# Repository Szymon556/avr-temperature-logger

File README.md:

# AVR Temperature Logger

Temperature logging system based on ATmega328P with:
- DS18B20 temperature sensor
- AT45DB041 DataFlash memory
- HD44780 LCD display

## Features

- Temperature acquisition
- SPI DataFlash storage
- LCD visualization
- AVR-GCC + Makefile build system avr-temperature-logger

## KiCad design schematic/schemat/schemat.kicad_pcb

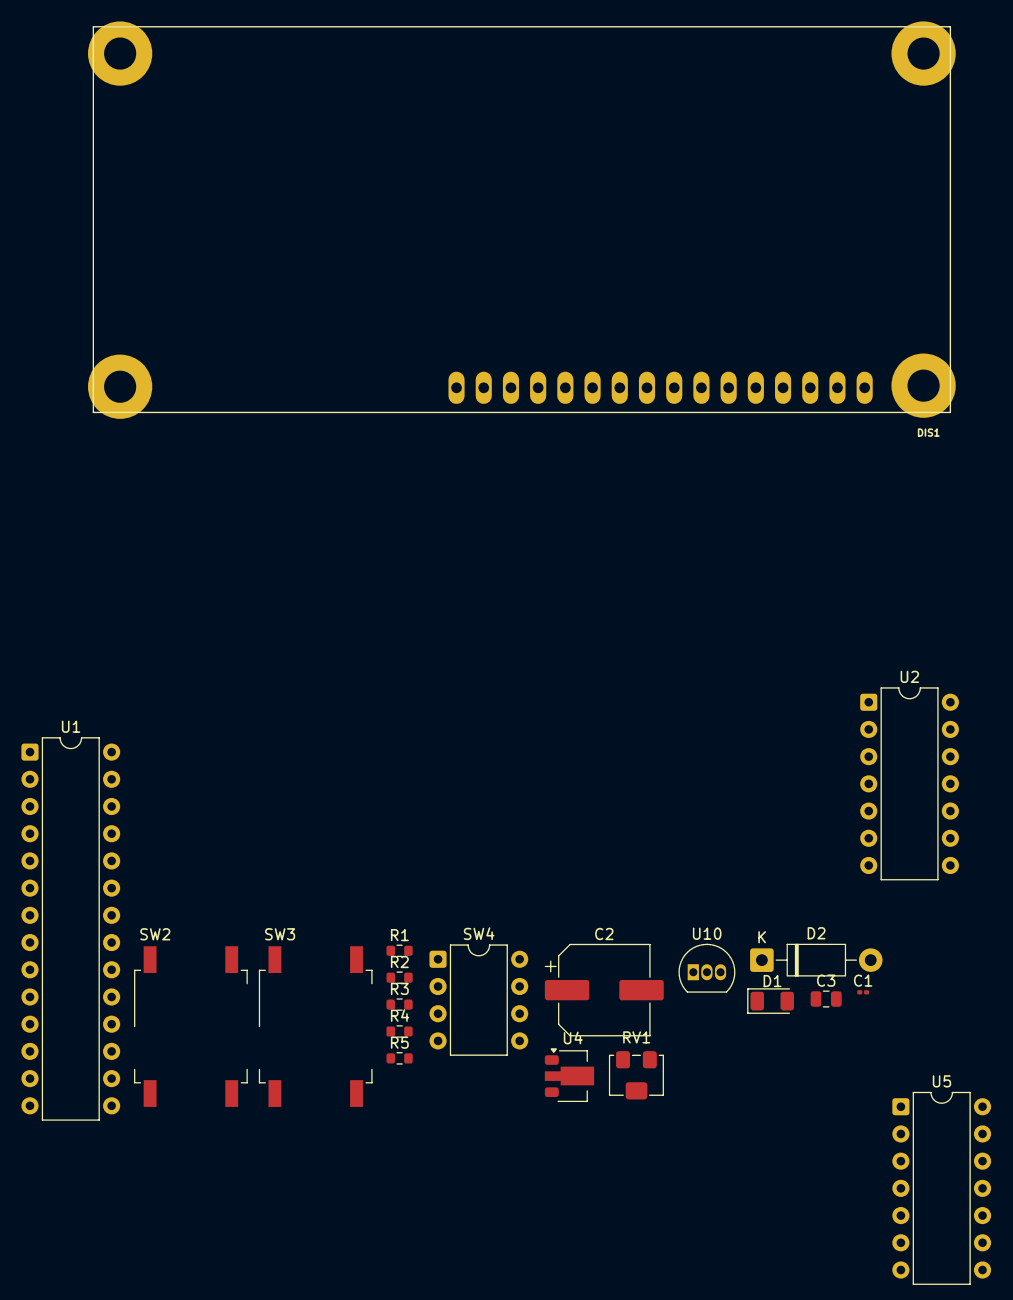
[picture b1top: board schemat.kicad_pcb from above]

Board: 2 copper layers, 20 parts (0 on the bottom side), 24 nets, no tracks yet.

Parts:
C1: 0.1uF; C_0201_0603Metric
C2: 1uF; CP_Elec_8x6.9
C3: 10uF; C_0805_2012Metric
D1: IR26-21C_L110_TR8; LED_1206_3216Metric
D2: 1N4001; D_DO-41_SOD81_P10.16mm_Horizontal
DIS1: HD44780; 16026-16X2
R1, R4: 100k; R_0603_1608Metric
R2: R_Trim; R_0603_1608Metric
R3, R5: 1k; R_0603_1608Metric
RV1: R_Potentiometer; Potentiometer_Bourns_3224W_Vertical
SW2, SW3: SW_MEC_5G; SW_MEC_5GSH9
SW4: SW_DIP_x01; DIP-8_W7.62mm
U1: ATmega328-P; DIP-28_W7.62mm
U2, U5: 74LS06; DIP-14_W7.62mm
U4: LM317L_SOT-89; SOT-89-3
U10: DS18B20; TO-92_Inline

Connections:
3.3V: C2.1, D1.2 (A), D2.2 (A), R1.1, R4.1, U4.2 (VO)
+5V: C3.1, DIS1.P$2, DIS1.P$15, R5.1, RV1.3, SW4.1, U1.7 (VCC), U1.20 (AVCC), U1.21 (AREF), U10.3 (V_{DD})
CS_High: U1.11 (PD5), U2.5
D4: DIS1.P$11, U1.27 (PC4)
D5: DIS1.P$12, U1.26 (PC3)
D6: DIS1.P$13, U1.25 (PC2)
D7: DIS1.P$14, U1.28 (PC5)
E: DIS1.P$6, U1.12 (PD6)
GND: C1.2, C2.2, C3.2, DIS1.P$1, DIS1.P$7, DIS1.P$8, DIS1.P$9, DIS1.P$10, DIS1.P$16, R1.2, R2.1, R2.2, R3.2, RV1.1, SW2.1 (A), SW2.2 (A), SW3.3 (B), SW3.4 (B), U1.8 (GND), U1.22 (GND), U4.1 (ADJ), U10.1 (GND)
unnamed: D1.1 (K), R3.1
unnamed: C1.1, D2.1 (K), SW4.2, U4.3 (VI)
unnamed: DIS1.P$3, RV1.2
unnamed: U1.23 (PC0), U10.2 (DQ)
unnamed: SW3.1 (A), SW3.2 (A), U1.13 (PD7)
unnamed: R5.2, SW2.3 (B), SW2.4 (B), U1.1 (~RESET/PC6)
unnamed: U2.2, U5.1
unnamed: U2.4, U5.3
unnamed: U2.6, U5.5
unnamed: U2.8, U5.9
RS: DIS1.P$4, U1.4 (PD2)
R\W: DIS1.P$5, U1.5 (PD3)
SCK_High: U1.6 (PD4), U2.3
SI_High: U1.3 (PD1), U2.1
SO_High: U1.2 (PD0), U2.9

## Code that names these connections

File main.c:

#include <stdlib.h>
#include <stdio.h>
#include <avr/io.h>
#include <util/delay.h>
#include <stdbool.h>
#include <avr/pgmspace.h>
#include "hd44780.h"
#include "SPI.h"
#include "DataFlash.h"
#include "AT45CMD.h"
#include "ds18b20.h"






void lcd_init();
void lcd_putchar(char);
void lcd_puttext_P(const char *txt);
void lcd_goto(uint8_t, uint8_t);
void lcd_defchar_P(uint8_t charno, const uint8_t *chardef);
void lcd_cls();
uint8_t SPI_SendByte(uint8_t byte);
int16_t convTemp(uint8_t *temp);

typedef struct{
        uint8_t ROM_ID[8];
        uint8_t TEMPERATURE[2];
}TEMPERATURE_DATA;



DataFLASH_Status DF_Status;
DataFLASH_ID DF_ID;
TEMPERATURE_DATA TMP_DATA;

void get_Temperature(TEMPERATURE_DATA *dataSave );
void show_Temp(TEMPERATURE_DATA *dataShow);
void DataFLASH_saveTemperature(TEMPERATURE_DATA *TMP_DATA);
void DataFLASH_getTemperature(TEMPERATURE_DATA *TMP_DATA);

int main(void){
    bool conf_ready = false; 
    //lcd_defchar_P(0,degree_char);
    lcd_init();
 
    lcd_puttext_P(PSTR("Pomiary Temperatury.\n"));
    conf_ready = initDS18B20();
    
    if(conf_ready){
        get_Temperature(&TMP_DATA);
            
    }
    

//Konfiguracja przycisku do pobierania danych
    DDRD &= ~(1 << PD7);
    PORTD |= (1 << PD7);
//KOnfiguracja lini SS
    DDRD |= (1 << PD5);
    SPI_init(300);
//Pobierz dane na temat producenta pamięci
    DataFLASH_SendCmd(AT45DBX_CMDC_RD_MNFCT_DEV_ID_SM,ADDRANDSIZE(DF_ID));
// Odczytaj aktualny rejestr statusu
    DataFLASH_SendCmd(AT45DBX_CMDC_RD_STATUS_REG,ADDRANDSIZE(DF_Status));
       

        while(1){
           _delay_ms(20);
           DataFLASH_saveTemperature(&TMP_DATA);
           if(!(PIND & (1 << PD7)))
           {
            _delay_ms(1);
            lcd_cls(); 
            lcd_puttext_P(PSTR("Pomiary Temperatury.\n"));  
            show_Temp(&TMP_DATA);     
            lcd_putchar(0xDF);
           }

    }
    return 0;
}

// Funkcja zapisująca temperaturę do pamięci.
void DataFLASH_saveTemperature(TEMPERATURE_DATA *TMP_DATA){
    get_Temperature(TMP_DATA);
    DataFLASH_SendCmdAddr(AT45DBX_CMDC_WR_BUF1,0,CS_Low);
    for(uint16_t i=0; i<256;i++)
    {   if(i > 2){
        SPI_SendByte(0);
         } else{
            SPI_SendByte(TMP_DATA->TEMPERATURE[i]);
        }

    }
    DataFLASH_CSEnable(false);



}

// Funkcja pobierająca temperaturę z pamięci
void DataFLASH_getTemperature(TEMPERATURE_DATA *TMP_DATA )
{
    uint8_t dummy[254];
    DataFLASH_SendCmdAddr(AT45DBX_CMDC_RD_BUF1_AF_SM,0,CS_Low);
    for(uint16_t i=0; i<256;i++){
        if(i > 2){
          dummy[i]=SPI_SendByte(0);
         } else{
            TMP_DATA->TEMPERATURE[i] = SPI_SendByte(0);
        }

    }
    DataFLASH_CSEnable(false);
    
}    

void lcd_init(){
    hd44780_init();
    hd44780_outcmd(HD44780_CLR);
    hd44780_wait_ready(1000);
    hd44780_outcmd(HD44780_ENTMODE(1,0));
    hd44780_wait_ready(1000);
    hd44780_outcmd(HD44780_DISPCTL(1,0,0));
    hd44780_wait_ready(1000);
}

void lcd_putchar(char c)
{
    static bool second_nl_seen;
    static uint8_t line = 0;
    if((second_nl_seen) && (c!='\n') && (line == 0)){
        hd44780_wait_ready(40);
        hd44780_outcmd(HD44780_CLR);
        hd44780_wait_ready(1600);
        second_nl_seen = false;
    }

    if(c == '\n'){
        if(line == 0){
            line++;
            hd44780_outcmd(HD44780_DDADDR(64));
            hd44780_wait_ready(1000);
        }else{
            second_nl_seen=true;
            line=0;
        }
    }else{
        hd44780_outdata(c);
        hd44780_wait_ready(40);
    }
}


void lcd_puttext_P(const char *txt){
   char ch;
   while((ch=pgm_read_byte(txt)))
   {
        lcd_putchar(ch);
        txt++;
   }
}



void lcd_goto(uint8_t x, uint8_t y){
    hd44780_outcmd(HD44780_DDADDR(0x40*y+x));
    hd44780_wait_ready(1000);
}

void lcd_cls(){
    hd44780_outcmd(HD44780_CLR);
    hd44780_wait_ready(false);
}


void lcd_defchar_P(uint8_t charno, const uint8_t *chardef){
    hd44780_outcmd(HD44780_CGADDR(charno*8));
    hd44780_wait_ready(false);
    for(uint8_t c=0;c < 8;c++){
        hd44780_outdata(pgm_read_byte(chardef));
        hd44780_wait_ready(false);
        chardef++;
    }
}


int16_t convTemp(uint8_t * temp){
    int16_t sum = 0;
    sum = temp[0] | (temp[1] << 8); 
    return sum;
 
}

void get_Temperature(TEMPERATURE_DATA *dataSave){
    sendCMD_DS18B20(DS18B20_READ_ROM);
    readData_DS18B20(8,dataSave->ROM_ID);
    initDS18B20();
    sendCMD_DS18B20(DS18B20_SKIP_ROM);
    sendCMD_DS18B20(DS18B20_START_CONV);
    togglePin_DS18B20();
    _delay_us(700);
    if(PINC & (1 << PC0)){
        initDS18B20();
        sendCMD_DS18B20(DS18B20_SKIP_ROM);
        sendCMD_DS18B20(DS18B20_READ_SCRATCHPAD);
        readData_DS18B20(2,dataSave->TEMPERATURE);
    }

}

void show_Temp(TEMPERATURE_DATA *dataShow){
    DataFLASH_getTemperature(dataShow);
    int16_t temp = 0;
    int16_t temp_int = 0;
    int8_t temp_frac = 0;
    char temp_buf[2] = {0x80,0x80};

    temp = convTemp(dataShow->TEMPERATURE);
    temp_int = temp >> 4; 
    itoa(temp_int,temp_buf,10);
    for(int i = 0; i < 2; i++)lcd_putchar(temp_buf[i]);
    lcd_putchar('.');
    temp_frac = ((temp & 0x0F) * 625) / 100;
    itoa(temp_frac,temp_buf,10);
    for(int i = 0; i < 2; i++)lcd_putchar(temp_buf[i]);

}


void SPI_init(unsigned int baud){
    // Najpierw ustaw 0, potem konfiguruj
    UBRR0 = 0;
    
    // Ustawienie wyjścia XCK0 (PD4) - kluczowe dla MSPI
    DDRD |= (1 << PD4);
    
    // UMSEL01 i UMSEL00 ustawiają tryb Master SPI
    UCSR0C = (1 << UMSEL01) | (1 << UMSEL00) | (0 << UCPHA0) | (0 << UCPOL0) | ( 0 << UDORD0 );
    
    // Włącz odbiornik i nadajnik
    UCSR0B = (1 << RXEN0) | (1 << TXEN0);
    
    // Ustaw prędkość (np. dla 1MHz przy 16MHz zegarze, baud powinno wynosić 7)
    UBRR0 = baud; 
}

uint8_t SPI_SendByte(uint8_t byte){
    
    // 1. Czekaj aż bufor nadawczy (UDR0) będzie gotowy na nowe dane
    while (!(UCSR0A & (1 << UDRE0)));

    // 2. Wyślij bajt
    UDR0 = byte;

    // 3. Czekaj aż flaga odbioru zostanie ustawiona (transmisja zakończona)
    while (!(UCSR0A & (1 << RXC0)));

    // 4. Zwróć odebrany bajt (odczyt czyści flagę RXC0)
    return UDR0;

}

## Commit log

2026-05-17 Add project to GitHub
2026-05-17 Add gitignore
2026-05-17 Remove build artefacts
